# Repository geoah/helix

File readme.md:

# Lesser Helix

A very compact, split, ortholinear, hot-swappable keyboard designed for use
with the nice!nano.

## Features

- Hotswap choc and mx sockets
- No TRRS jack
- Battery switch

## Credits

- [MakotoKurauchi](https://github.com/MakotoKurauchi/helix)
- [McMadhatter](https://github.com/mcmadhatter/helix)

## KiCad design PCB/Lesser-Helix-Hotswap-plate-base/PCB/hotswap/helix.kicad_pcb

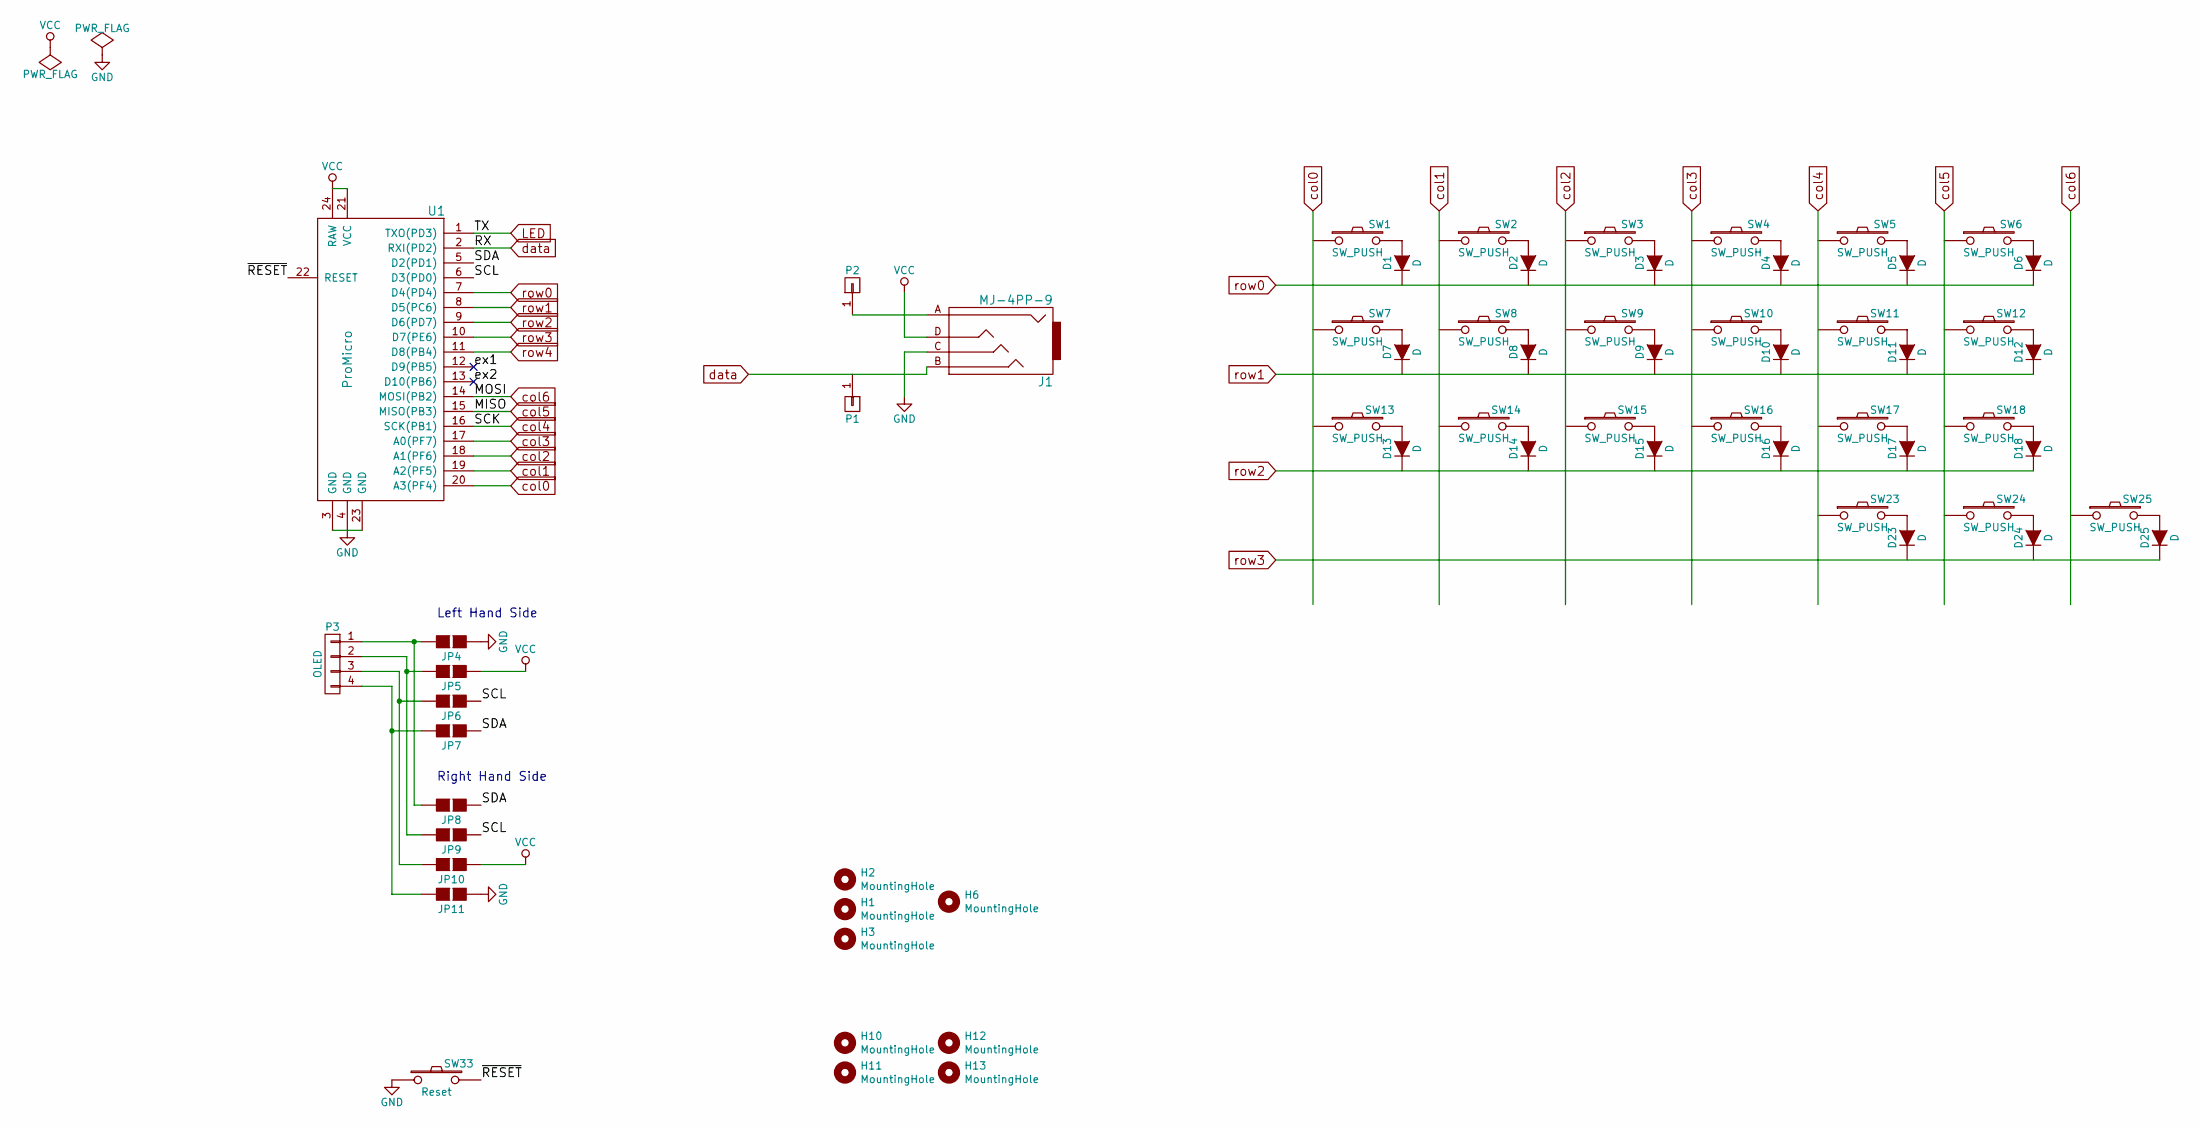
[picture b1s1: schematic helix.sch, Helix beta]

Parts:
D1, D2, D3, D4, D5, D6, D7, D8, D9, D10, D11, D12, D13, D14, D15, D16, D17, D18, D23, D24, D25: D; D3_TH_SMD
H1, H2, H3, H6: MountingHole; HOLE_M2_TH
H10, H11, H12, H13: MountingHole; HOLE_M2
J1: MJ-4PP-9; MJ-4PP-9_rev2
JP4, JP11: GND; Jumper
JP5, JP10: VCC; Jumper
JP6, JP9: SCL; Jumper
JP7, JP8: SDA; Jumper
P1, P2: CONN_01X01; 1PIN_0.1
P3: OLED; MY_SIL-4
SW1, SW2, SW3, SW4, SW5, SW6, SW7, SW8, SW9, SW10, SW11, SW12, SW13, SW14, SW15, SW16, SW17, SW18, SW23, SW24, SW25: SW_PUSH; MXOnly-1U-Hotswap-Double-noled
SW33: Reset; SW_3.5x6.0_TH
U1: ProMicro; ProMicro_rev

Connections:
/SCL: JP6.1 (G1), JP9.1 (G1), U1.6 (D3(PD0)); also elsewhere on the board
/SDA: JP7.1 (G1), JP8.1 (G1), U1.5 (D2(PD1)); also elsewhere on the board
/ex1: U1.12 (D9(PB5)); also elsewhere on the board
/ex2: U1.13 (D10(PB6)); also elsewhere on the board
/~RESET: SW33.2, U1.22 (RESET); also elsewhere on the board
LED: U1.1 (TXO(PD3)); also elsewhere on the board
unnamed: D1.2 (A), SW1.2
unnamed: D2.2 (A), SW2.2
unnamed: D3.2 (A), SW3.2
unnamed: D4.2 (A), SW4.2
unnamed: D5.2 (A), SW5.2
unnamed: D6.2 (A), SW6.2
unnamed: D7.2 (A), SW7.2
unnamed: D8.2 (A), SW8.2
unnamed: D9.2 (A), SW9.2
unnamed: D10.2 (A), SW10.2
unnamed: D11.2 (A), SW11.2
unnamed: D12.2 (A), SW12.2
unnamed: D13.2 (A), SW13.2
unnamed: D14.2 (A), SW14.2
unnamed: D15.2 (A), SW15.2
unnamed: D16.2 (A), SW16.2
unnamed: D17.2 (A), SW17.2
unnamed: D18.2 (A), SW18.2
unnamed: D23.2 (A), SW23.2
unnamed: D24.2 (A), SW24.2
unnamed: D25.2 (A), SW25.2
unnamed: J1.A, P2.1
unnamed: JP4.2 (G2), JP8.2 (G2), P3.1
unnamed: JP5.2 (G2), JP9.2 (G2), P3.2
unnamed: JP6.2 (G2), JP10.2 (G2), P3.3
unnamed: JP7.2 (G2), JP11.2 (G2), P3.4
VCC: J1.D, JP5.1 (G1), JP10.1 (G1), U1.21 (VCC), U1.24 (RAW); also elsewhere on the board
col0: U1.20 (A3(PF4)); also elsewhere on the board
col1: U1.19 (A2(PF5)); also elsewhere on the board
col2: U1.18 (A1(PF6)); also elsewhere on the board
col3: U1.17 (A0(PF7)); also elsewhere on the board
col4: U1.16 (SCK(PB1)); also elsewhere on the board
col5: U1.15 (MISO(PB3)); also elsewhere on the board
col6: U1.14 (MOSI(PB2)); also elsewhere on the board
data: J1.B, U1.2 (RXI(PD2)); also elsewhere on the board
row0: D6.1 (K), U1.7 (D4(PD4)); also elsewhere on the board
row1: D12.1 (K), U1.8 (D5(PC6)); also elsewhere on the board
row2: D18.1 (K), U1.9 (D6(PD7)); also elsewhere on the board
row3: D25.1 (K), U1.10 (D7(PE6)); also elsewhere on the board
row4: U1.11 (D8(PB4)); also elsewhere on the board

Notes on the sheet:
Left Hand Side
Right Hand Side

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
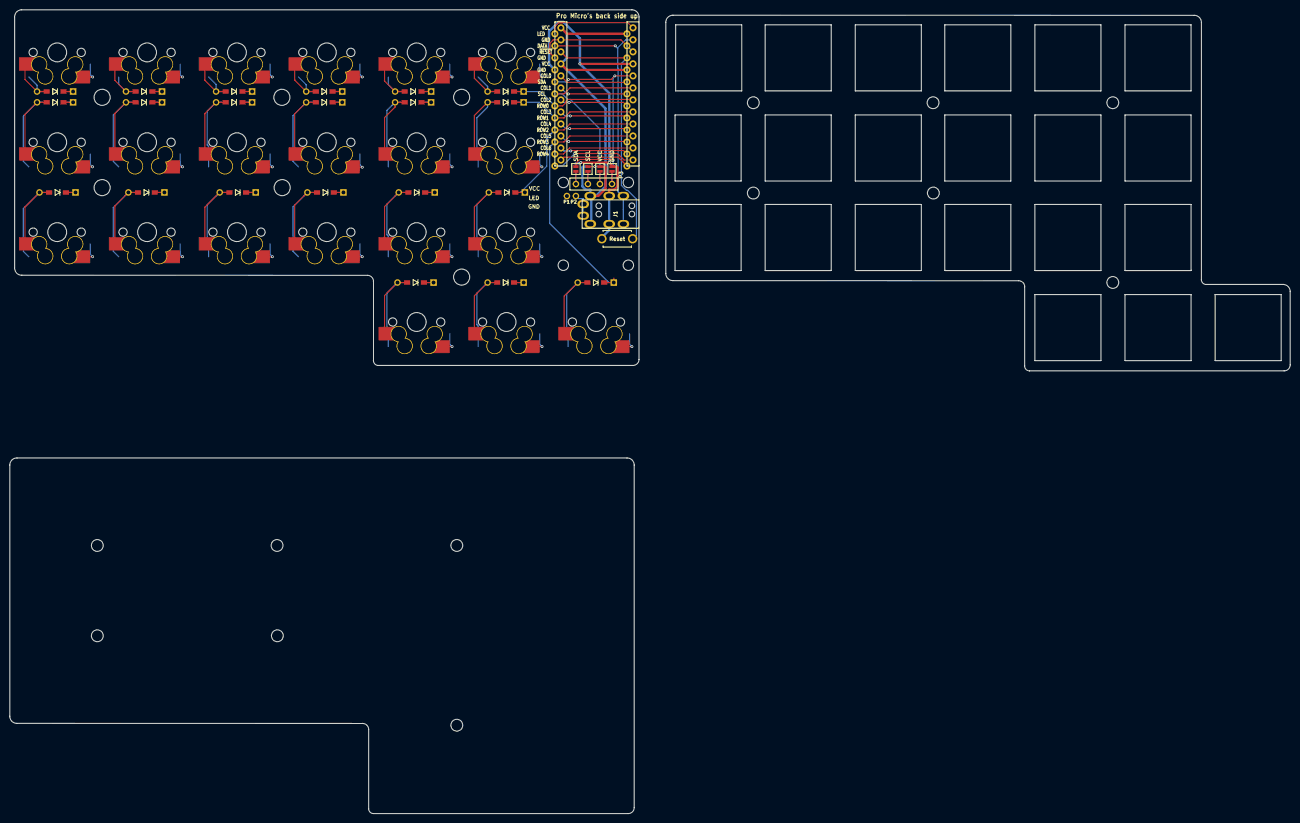
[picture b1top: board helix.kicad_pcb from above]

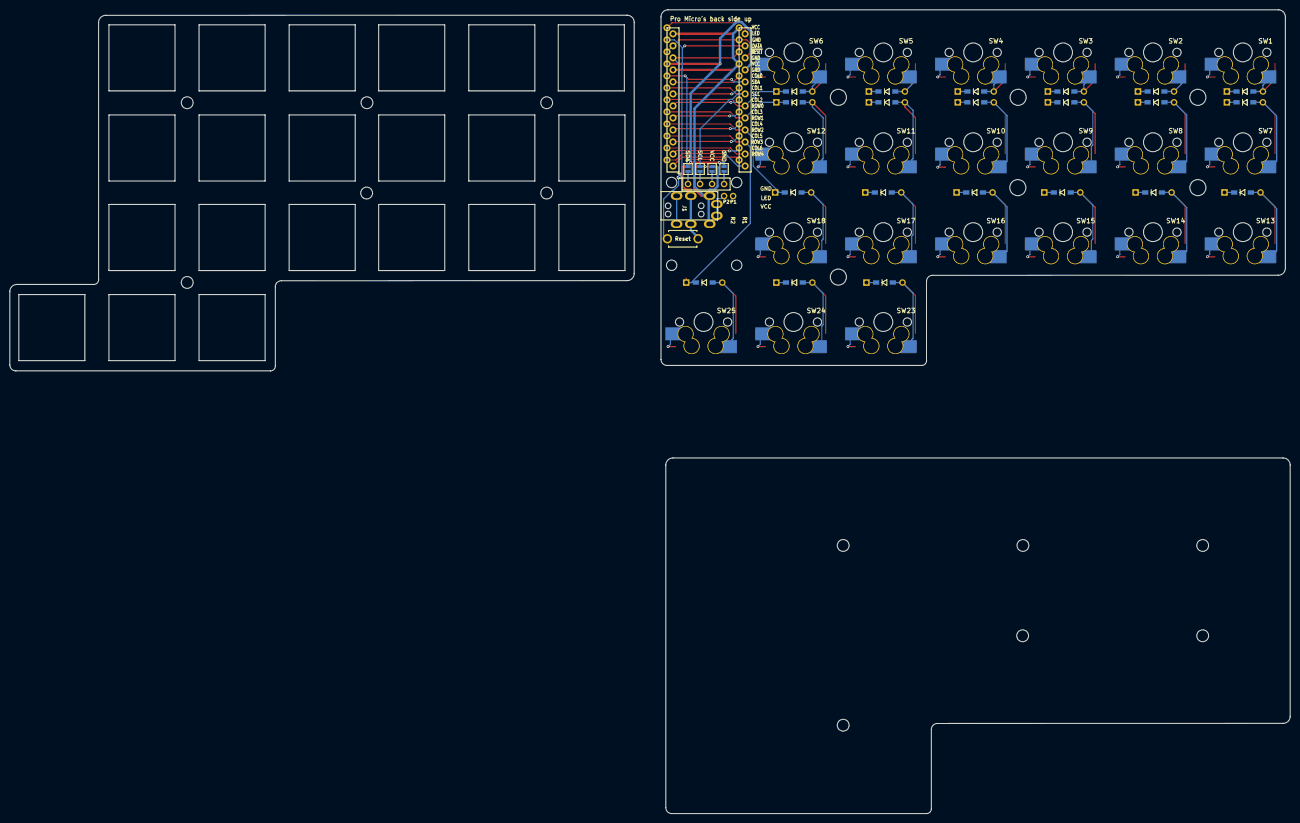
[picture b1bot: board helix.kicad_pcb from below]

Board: 2 copper layers, 270.7 x 169.9 mm, 79 parts (5 on the bottom side), 48 nets.

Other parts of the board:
H1#2, H1#3, H1#4, H1#5, H1#6, H1#7, H1#8, H1#9, H2#2, H2#3, H3#2, H3#3, H6#2, H6#3: MountingHole; HOLE_M2_TH
U1a: ProMicro; ProMicro_rev

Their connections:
/SCL: U1a.6; also elsewhere on the board
/SDA: U1a.5; also elsewhere on the board
/ex1: U1a.12; also elsewhere on the board
/ex2: U1a.13; also elsewhere on the board
/~RESET: U1a.22; also elsewhere on the board
LED: U1a.1; also elsewhere on the board
VCC: U1a.21, U1a.24; also elsewhere on the board
col0: U1a.20; also elsewhere on the board
col1: U1a.19; also elsewhere on the board
col2: U1a.18; also elsewhere on the board
col3: U1a.17; also elsewhere on the board
col4: U1a.16; also elsewhere on the board
col5: U1a.15; also elsewhere on the board
col6: U1a.14; also elsewhere on the board
data: U1a.2; also elsewhere on the board
row0: U1a.7; also elsewhere on the board
row1: U1a.8; also elsewhere on the board
row2: U1a.9; also elsewhere on the board
row3: U1a.10; also elsewhere on the board
row4: U1a.11; also elsewhere on the board

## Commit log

2020-11-24 feat: add lesser helix v0.6.0
2020-11-24 chore: remove unused folders, fix licence, fix readme
